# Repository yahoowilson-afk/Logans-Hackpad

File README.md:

# Logans-Hackpad
 This is my hackpad (macropad). I plan on using it for music, something with games and possibly streaming, I have 6 switches that are programmable to keys on a keyboard and this is one of the first projects of this kind that I have ever done.

Bill of Materials:

    4x Cherry MX Switches
    1x XIAO RP2040
    4x Blank DSA Keycaps
    4x M3x16 Bolt
    4x M3 Heatset

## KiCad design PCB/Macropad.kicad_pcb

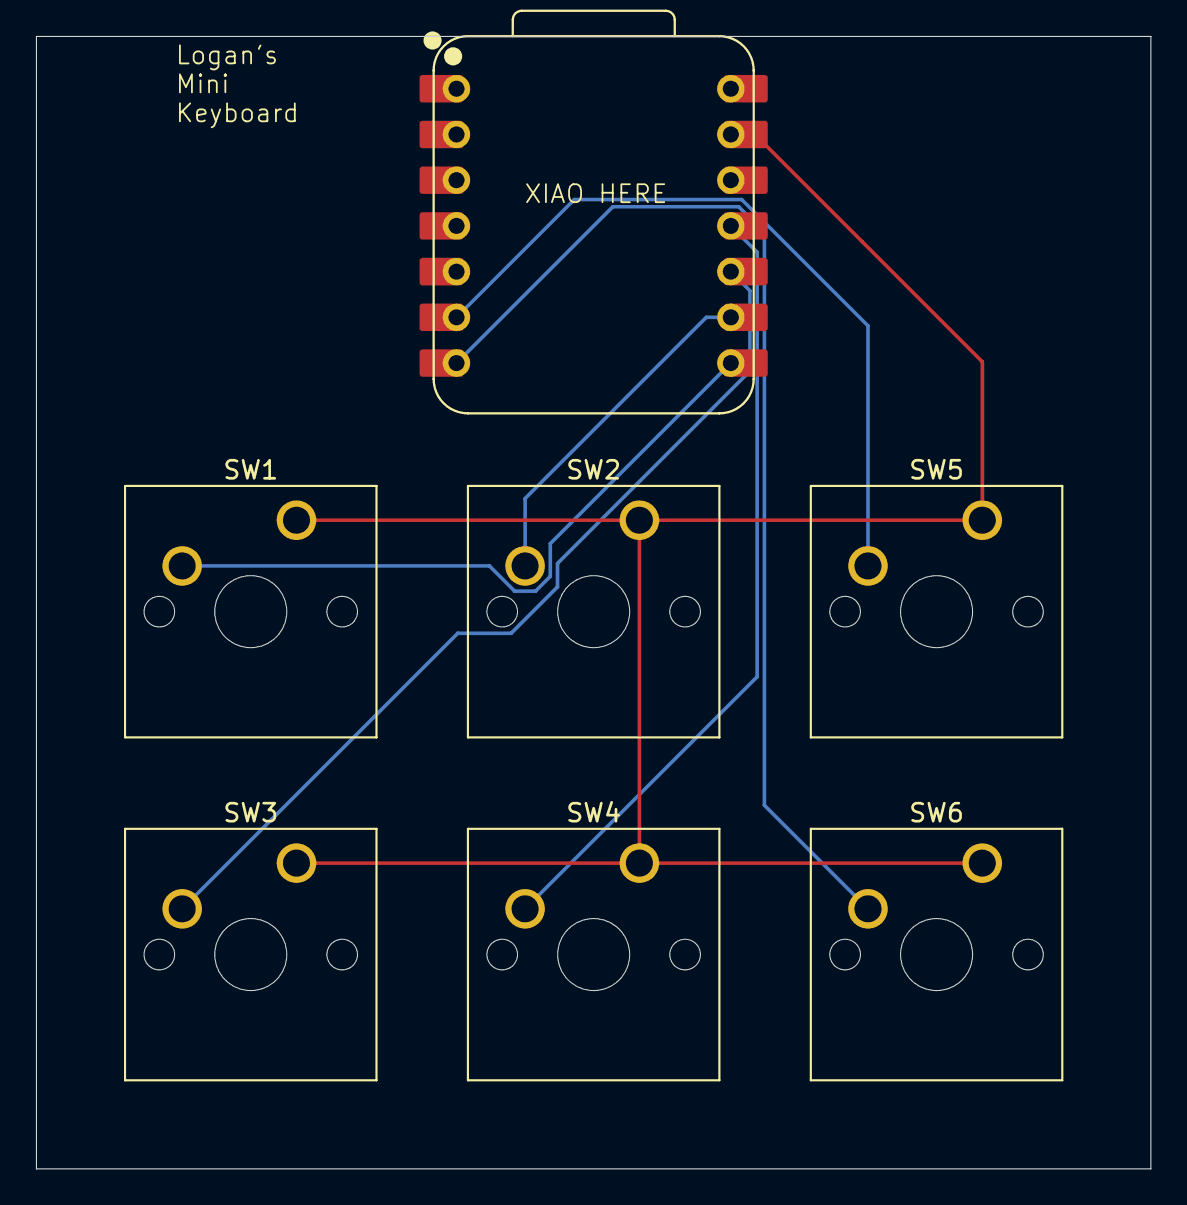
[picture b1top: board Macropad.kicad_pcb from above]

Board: 2 copper layers, 61.9 x 62.9 mm, 7 parts (0 on the bottom side), 7 nets.

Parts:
SW1, SW2, SW3, SW4, SW5, SW6: SW_Push; SW_Cherry_MX_1.00u_PCB
U1: XIAO-RP2040-DIP

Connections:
GND: SW1.1, SW2.1, SW3.1, SW4.1, SW5.1, SW6.1, U1.13 (GND)
unnamed: SW6.2, U1.7 (GPIO0/TX)
unnamed: SW1.2, U1.8 (GPIO1/RX)
unnamed: SW2.2, U1.9 (GPIO2/SCK)
unnamed: SW4.2, U1.11 (GPIO3/MOSI)
unnamed: SW3.2, U1.10 (GPIO4/MISO)
unnamed: SW5.2, U1.6 (GPIO7/SCL)

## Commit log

2025-12-06 Update README with project description
    Added a brief description of the hackpad project.
2025-12-06 Rename bottom case.step to CAD/bottom case.step
2025-12-06 Add to CAD Folder
2025-12-06 add cad files to folder
2025-12-06 Rename Macropad.kicad_pcb to PCB/Macropad.kicad_pcb
2025-12-07 added firmware
2025-12-07 Add images to README
    Added images to enhance the README documentation.
2025-12-07 Add images for case in README
    Added additional images for the top case of the hackpad.
2025-12-07 Add schematic image to README
    Updated the README to include a schematic image.
2025-12-07 added case images
2025-12-07 fixed error
2025-12-07 added to cad folder
2025-12-07 Deleted bad firmware
2025-12-07 fixed firmware
2025-12-07 added to folder
2025-12-07 Add Bill of Materials to README
    Added a Bill of Materials section with components listed.
2025-12-07 added new case images
2025-12-07 added new KiCAD files
2025-12-07 new cad files
2025-12-07 added updated cad step files
2025-12-08 adding new pcb
2025-12-08 new pcb file
2025-12-08 deleted bad step case
2025-12-08 Added new image of case.
    added new image with 3d models in fusion and no LEDs because I don't really need them.
